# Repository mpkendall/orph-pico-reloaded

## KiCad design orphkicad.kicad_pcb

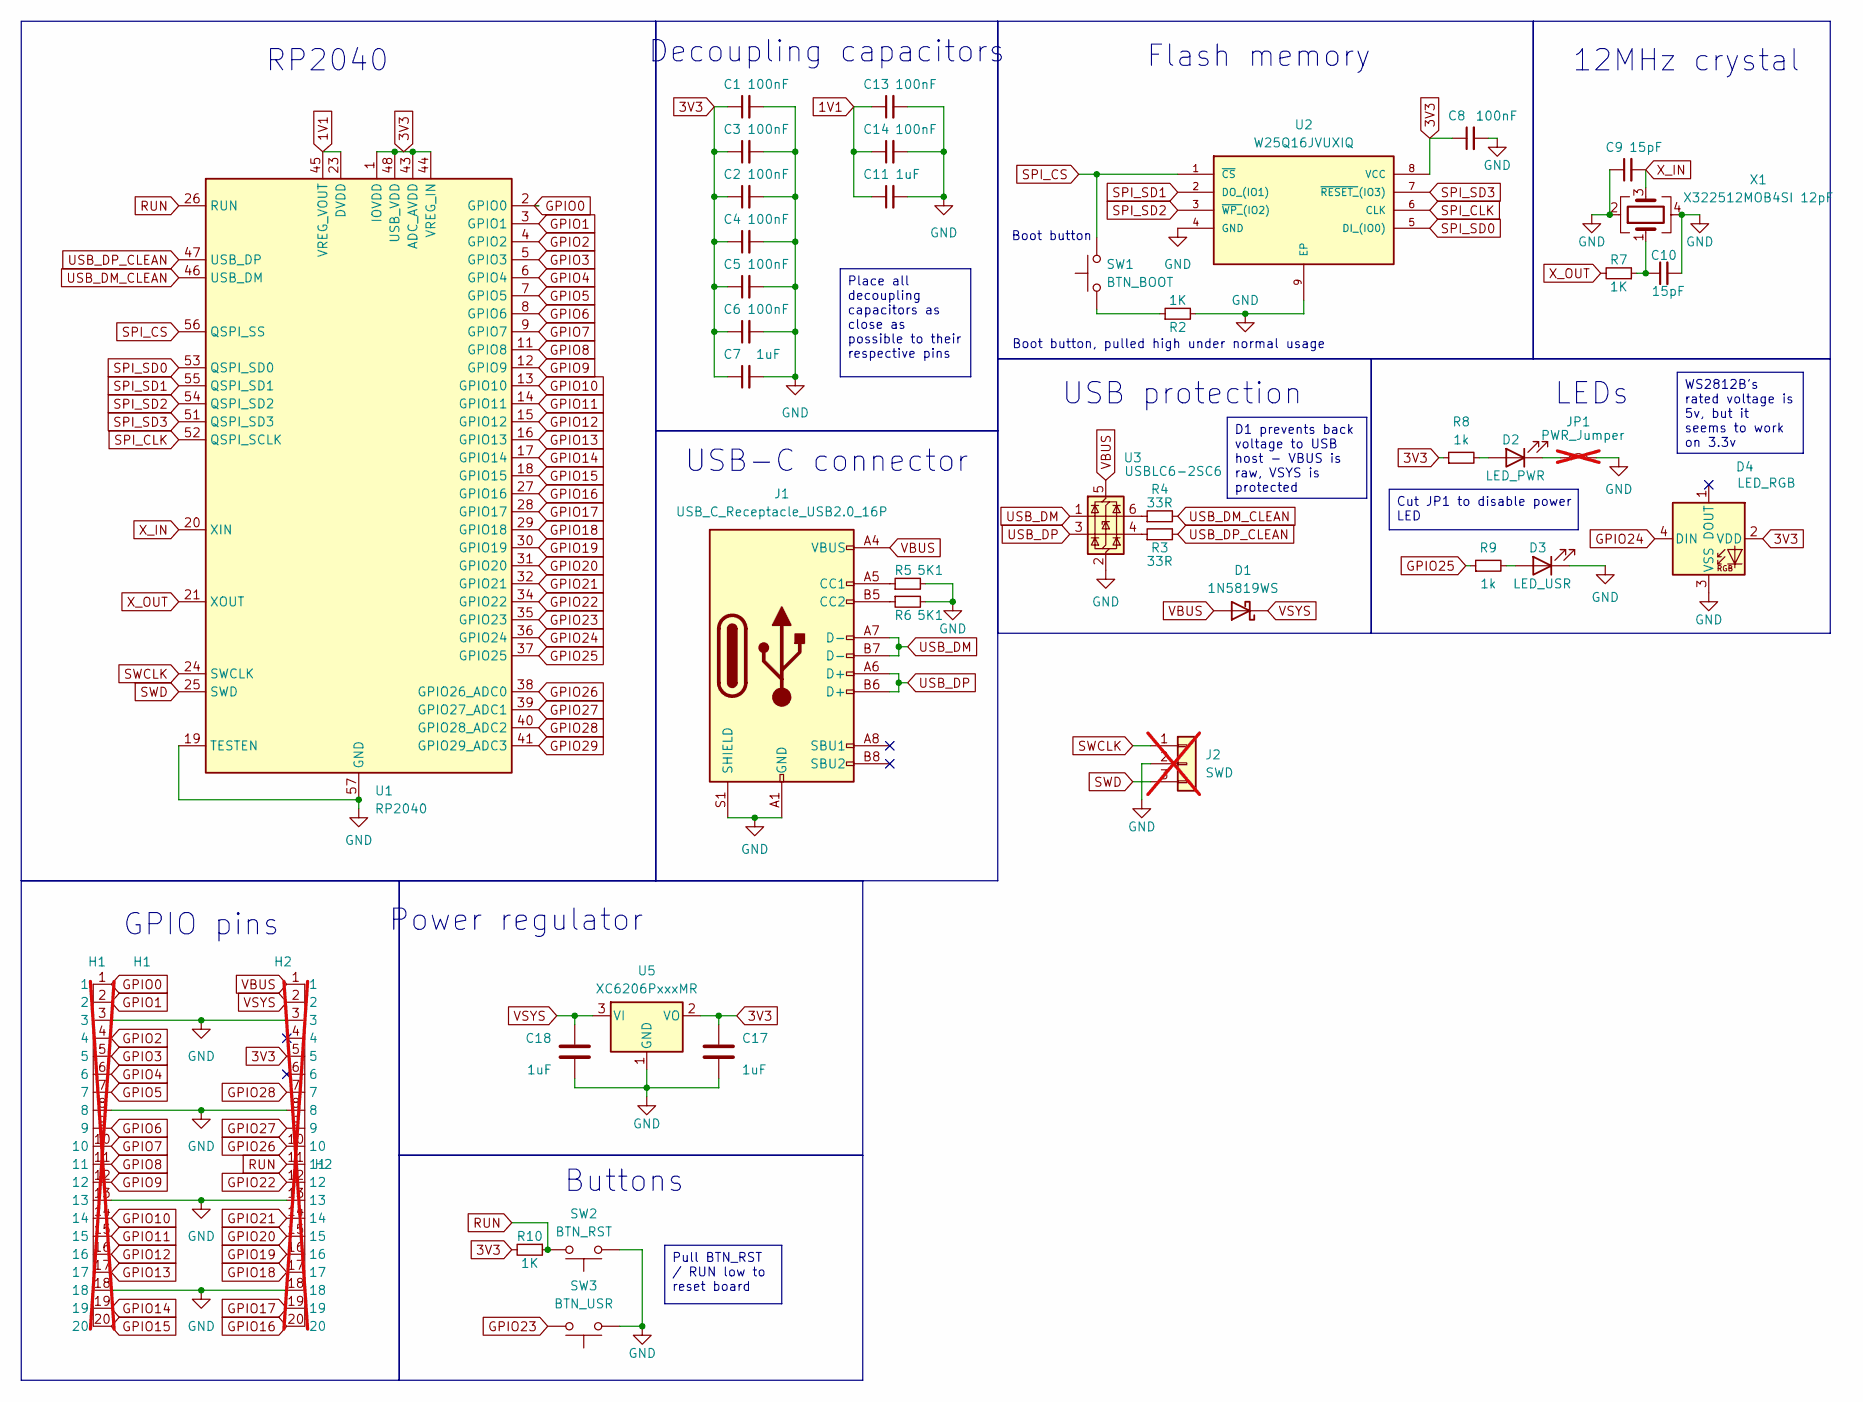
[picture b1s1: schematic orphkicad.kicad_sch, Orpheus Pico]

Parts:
C1, C2, C3, C4, C5, C6, C8, C13, C14: 100nF; C_0402_1005Metric; LCSC C1525
C7, C11, C17, C18: 1uF; C_0402_1005Metric; LCSC C52923
C9, C10: 15pF; C_0402_1005Metric; LCSC C1548
D1: 1N5819WS; D_SOD-323; LCSC C191023
D2: LED_PWR; LED_0603_1608Metric; LCSC C2286
D3: LED_USR; LED_0603_1608Metric; LCSC C2286
D4: LED_RGB; LED-SMD_4P-L1.6-W1.5_XL-1615RGBC-WS2812B; LCSC C5349954
H1: H1; OrphPicoHeaders; not fitted
H2: H2; OrphPicoHeaders; not fitted
J1: USB_C_Receptacle_USB2.0_16P; USB-C-SMD_TYPE-C-6PIN-2MD-073; LCSC C2765186
J2: SWD; PinHeader_1x03_P2.54mm_Vertical; not fitted
JP1: PWR_Jumper; SolderJumper-2_P1.3mm_Bridged2Bar_RoundedPad1.0x1.5mm; not fitted
R2, R7, R10: 1K; R_0402_1005Metric; LCSC C11702
R3, R4: 33R; R_0402_1005Metric; LCSC C25105
R5, R6: 5K1; R_0402_1005Metric; LCSC C25905
R8, R9: 1k; R_0402_1005Metric; LCSC C11702
SW1: BTN_BOOT; SW-SMD_L3.9-W3.0-P4.45; LCSC C455280
SW2: BTN_RST; SW-SMD_L3.9-W3.0-P4.45; LCSC C455280
SW3: BTN_USR; SW-SMD_L3.9-W3.0-P4.45; LCSC C455280
U1: RP2040; QFN-56-1EP_7x7mm_P0.4mm_EP3.2x3.2mm; LCSC C2040
U2: W25Q16JVUXIQ; Winbond_USON-8-1EP_3x2mm_P0.5mm_EP0.2x1.6mm; MANUFACTURER_PART_NUMBER W25Q16JVUXIQ; LCSC C2843335
U3: USBLC6-2SC6; SOT-23-6; LCSC C5180249
U5: XC6206PxxxMR; SOT-23-3; LCSC C5446
X1: X322512MOB4SI 12pF; Crystal_SMD_3225-4Pin_3.2x2.5mm; LCSC C70565

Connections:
1V1: C11.1, C13.1, C14.1, U1.23 (DVDD), U1.45 (VREG_VOUT), U1.50 (DVDD)
3V3: C1.1, C2.1, C3.1, C4.1, C5.1, C6.1, C7.1, C8.1, C17.1, D4.2 (VDD), H2.5, R8.1, R10.2, U1.1 (IOVDD), U1.10 (IOVDD), U1.22 (IOVDD), U1.33 (IOVDD), U1.42 (IOVDD), U1.43 (ADC_AVDD), U1.44 (VREG_IN), U1.48 (USB_VDD), U1.49 (IOVDD), U2.8 (VCC), U5.2 (VO)
GND: C1.2, C2.2, C3.2, C4.2, C5.2, C6.2, C7.2, C8.2, C9.1, C10.2, C11.2, C13.2, C14.2, C17.2, C18.2, D3.1 (K), D4.3 (VSS), H1.3, H1.8, H1.13, H1.18, H2.3, H2.8, H2.13, H2.18, J1.A1 (GND), J1.B1 (GND), J1.S1 (SHIELD), J2.2, JP1.2 (B), R2.2, R5.2, R6.2, SW2.1, SW3.1, U1.19 (TESTEN), U1.57 (GND), U2.4 (GND), U2.9 (EP), U3.2 (GND), U5.1 (GND), X1.2, X1.4
GPIO0: H1.1, U1.2 (GPIO0)
GPIO1: H1.2, U1.3 (GPIO1)
GPIO2: H1.4, U1.4 (GPIO2)
GPIO3: H1.5, U1.5 (GPIO3)
GPIO4: H1.6, U1.6 (GPIO4)
GPIO5: H1.7, U1.7 (GPIO5)
GPIO6: H1.9, U1.8 (GPIO6)
GPIO7: H1.10, U1.9 (GPIO7)
GPIO8: H1.11, U1.11 (GPIO8)
GPIO9: H1.12, U1.12 (GPIO9)
GPIO10: H1.14, U1.13 (GPIO10)
GPIO11: H1.15, U1.14 (GPIO11)
GPIO12: H1.16, U1.15 (GPIO12)
GPIO13: H1.17, U1.16 (GPIO13)
GPIO14: H1.19, U1.17 (GPIO14)
GPIO15: H1.20, U1.18 (GPIO15)
GPIO16: H2.20, U1.27 (GPIO16)
GPIO17: H2.19, U1.28 (GPIO17)
GPIO18: H2.17, U1.29 (GPIO18)
GPIO19: H2.16, U1.30 (GPIO19)
GPIO20: H2.15, U1.31 (GPIO20)
GPIO21: H2.14, U1.32 (GPIO21)
GPIO22: H2.12, U1.34 (GPIO22)
GPIO23: SW3.2, U1.35 (GPIO23)
GPIO24: D4.4 (DIN), U1.36 (GPIO24)
GPIO25: R9.1, U1.37 (GPIO25)
GPIO26: H2.10, U1.38 (GPIO26_ADC0)
GPIO27: H2.9, U1.39 (GPIO27_ADC1)
GPIO28: H2.7, U1.40 (GPIO28_ADC2)
GPIO29: U1.41 (GPIO29_ADC3)
unnamed: C10.1, R7.1, X1.1
unnamed: D2.2 (A), R8.2
unnamed: D2.1 (K), JP1.1 (A)
unnamed: D3.2 (A), R9.2
unnamed: J1.A5 (CC1), R5.1
unnamed: J1.B5 (CC2), R6.1
unnamed: R2.1, SW1.1
unnamed: R3.1, U3.4 (I/O2)
unnamed: R4.1, U3.6 (I/O1)
RUN: H2.11, R10.1, SW2.2, U1.26 (RUN)
SPI_CLK: U1.52 (QSPI_SCLK), U2.6 (CLK)
SPI_CS: SW1.2, U1.56 (QSPI_SS), U2.1 (~CS)
SPI_SD0: U1.53 (QSPI_SD0), U2.5 (DI_(IO0))
SPI_SD1: U1.55 (QSPI_SD1), U2.2 (DO_(IO1))
SPI_SD2: U1.54 (QSPI_SD2), U2.3 (~WP_(IO2))
SPI_SD3: U1.51 (QSPI_SD3), U2.7 (~RESET_(IO3))
SWCLK: J2.1, U1.24 (SWCLK)
SWD: J2.3, U1.25 (SWD)
USB_DM: J1.A7 (D-), J1.B7 (D-), U3.1 (I/O1)
USB_DM_CLEAN: R4.2, U1.46 (USB_DM)
USB_DP: J1.A6 (D+), J1.B6 (D+), U3.3 (I/O2)
USB_DP_CLEAN: R3.2, U1.47 (USB_DP)
VBUS: D1.2 (A), H2.1, J1.A4 (VBUS), J1.B4 (VBUS), U3.5 (VBUS)
VSYS: C18.1, D1.1 (K), H2.2, U5.3 (VI)
X_IN: C9.2, U1.20 (XIN), X1.3
X_OUT: R7.2, U1.21 (XOUT)

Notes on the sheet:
Power regulator
Flash memory
Boot button, pulled high under normal usage
USB-C connector
Decoupling capacitors
USB protection
LEDs
Boot button
RP2040
GPIO pins
Buttons
12MHz crystal
Pull BTN_RST / RUN low to reset board
Place all decoupling capacitors as close as possible to their respective pins
WS2812B's rated voltage is 5v, but it seems to work on 3.3v
Cut JP1 to disable power LED
D1 prevents back voltage to USB host - VBUS is raw, VSYS is protected

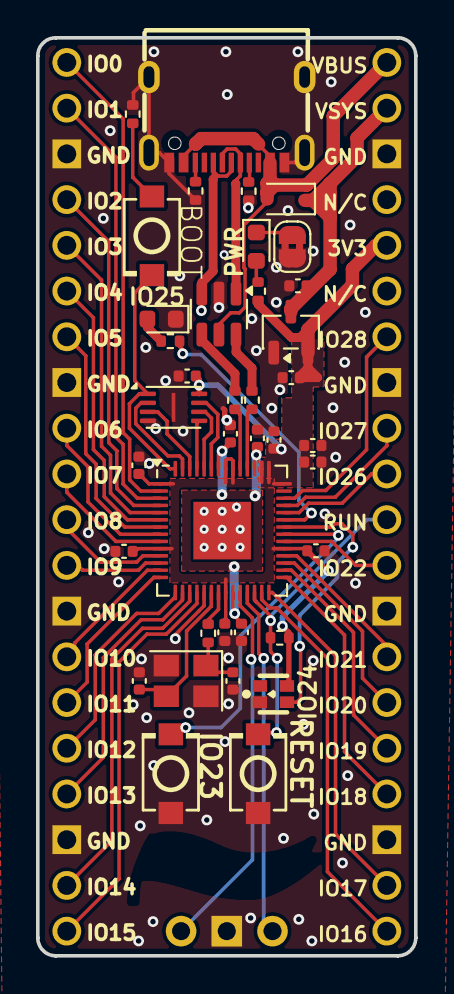
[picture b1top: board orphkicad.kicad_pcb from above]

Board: 2 copper layers, 21.0 x 51.0 mm, 41 parts (0 on the bottom side), 58 nets.

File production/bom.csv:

Designator,Footprint,Quantity,Value,LCSC Part #
"C1, C13, C14, C2, C3, C4, C5, C6, C8",0402,9,100nF,C1525
"C10, C9",0402,2,15pF,C1548
"C11, C17, C18, C7",0402,4,1uF,C52923
D1,D_SOD-323,1,1N5819WS,C191023
D2,0603,1,LED_PWR,C2286
D3,0603,1,LED_USR,C2286
D4,LED-SMD_4P-L1.6-W1.5_XL-1615RGBC-WS2812B,1,LED_RGB,C5349954
J1,USB-C-SMD_TYPE-C-6PIN-2MD-073,1,USB_C_Receptacle_USB2.0_16P,C2765186
"R10, R2, R7, R8, R9",0402,5,1K,C11702
"R3, R4",0402,2,33R,C25105
"R5, R6",0402,2,5K1,C25905
SW1,SW-SMD_L3.9-W3.0-P4.45,1,BTN_BOOT,C455280
SW2,SW-SMD_L3.9-W3.0-P4.45,1,BTN_RST,C455280
SW3,SW-SMD_L3.9-W3.0-P4.45,1,BTN_USR,C455280
U1,QFN-56-1EP_7x7mm_P0.4mm_EP3.2x3.2mm,1,RP2040,C2040
U2,Winbond_USON-8-1EP_3x2mm_P0.5mm_EP0.2x1.6mm,1,W25Q16JVUXIQ,C2843335
U3,SOT-23-6,1,USBLC6-2SC6,C5180249
U5,SOT-23-3,1,XC6206PxxxMR,C5446
X1,Crystal_SMD_3225-4Pin_3.2x2.5mm,1,X322512MOB4SI 12pF,C70565

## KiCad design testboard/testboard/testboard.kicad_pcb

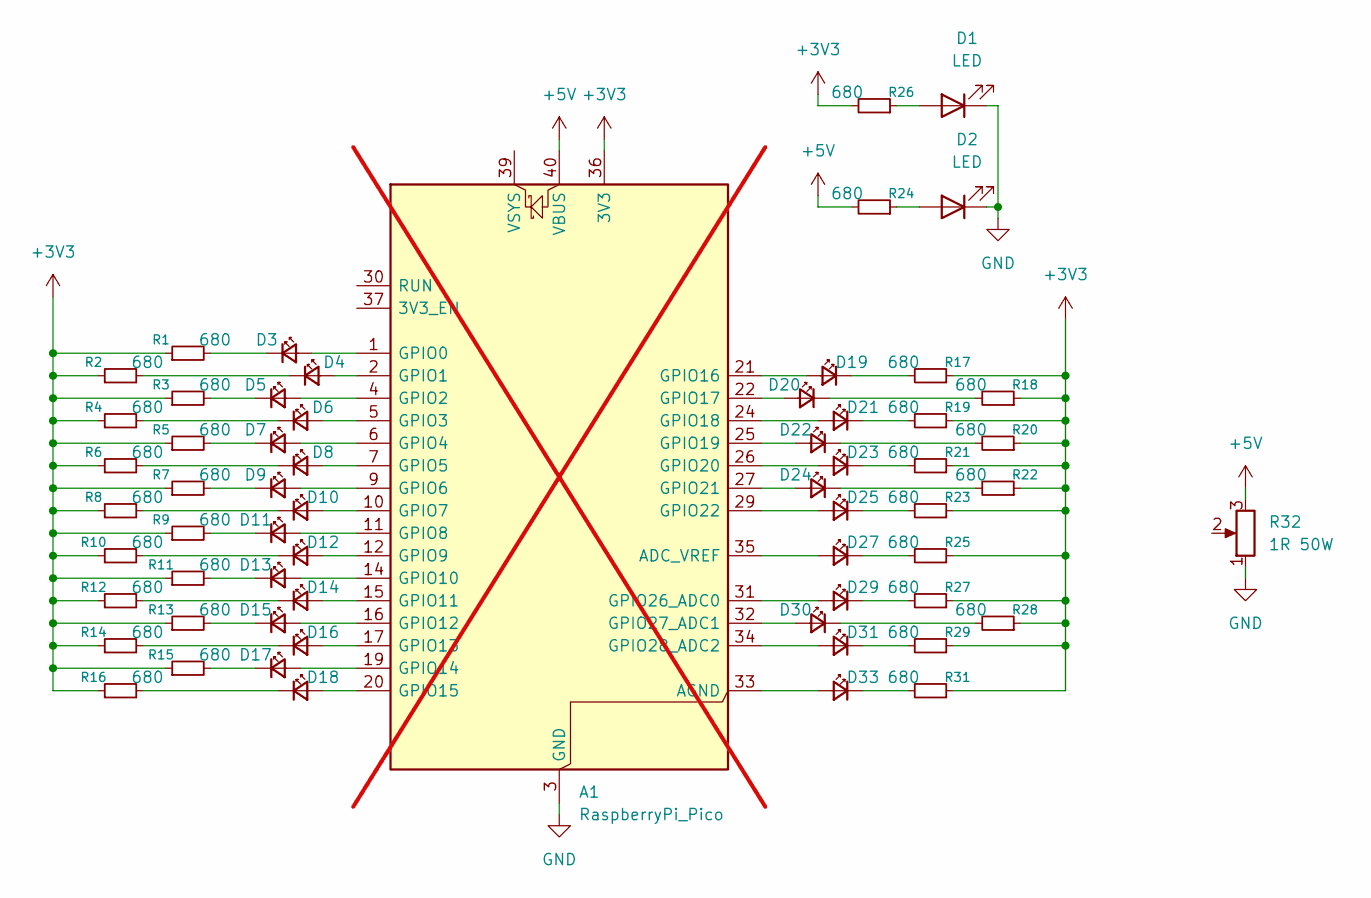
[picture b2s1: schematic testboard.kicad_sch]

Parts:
A1: RaspberryPi_Pico; RaspberryPi_Pico_Common_THT; not fitted
D1, D2, D3, D4, D5, D6, D7, D8, D9, D10, D11, D12, D13, D14, D15, D16, D17, D18, D19, D20, D21, D22, D23, D24, D25, D27, D29, D30, D31, D33: LED; LED_0603_1608Metric; LCSC Part # C2290
R1, R2, R3, R4, R5, R6, R7, R8, R9, R10, R11, R12, R13, R14, R15, R16, R17, R18, R19, R20, R21, R22, R23, R24, R25, R26, R27, R28, R29, R31: 680; R_0603_1608Metric; LCSC Part # C23228
R32: 1R 50W; TO-263-2; LCSC Part # C39221240

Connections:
+3V3: A1.36 (3V3), R1.1, R2.1, R3.1, R4.1, R5.1, R6.1, R7.1, R8.1, R9.1, R10.1, R11.1, R12.1, R13.1, R14.1, R15.1, R16.1, R17.1, R18.1, R19.1, R20.1, R21.1, R22.1, R23.1, R25.1, R26.2, R27.1, R28.1, R29.1, R31.1
+5V: A1.40 (VBUS), R24.2, R32.3
GND: A1.3 (GND), A1.8 (GND), A1.13 (GND), A1.18 (GND), A1.23 (GND), A1.28 (GND), A1.38 (GND), D1.1 (K), D2.1 (K), R32.1
unnamed: A1.35 (ADC_VREF), D27.2 (A)
unnamed: A1.33 (AGND), D33.2 (A)
unnamed: A1.1 (GPIO0), D3.2 (A)
unnamed: A1.2 (GPIO1), D4.2 (A)
unnamed: A1.4 (GPIO2), D5.2 (A)
unnamed: A1.5 (GPIO3), D6.2 (A)
unnamed: A1.6 (GPIO4), D7.2 (A)
unnamed: A1.7 (GPIO5), D8.2 (A)
unnamed: A1.9 (GPIO6), D9.2 (A)
unnamed: A1.10 (GPIO7), D10.2 (A)
unnamed: A1.11 (GPIO8), D11.2 (A)
unnamed: A1.12 (GPIO9), D12.2 (A)
unnamed: A1.14 (GPIO10), D13.2 (A)
unnamed: A1.15 (GPIO11), D14.2 (A)
unnamed: A1.16 (GPIO12), D15.2 (A)
unnamed: A1.17 (GPIO13), D16.2 (A)
unnamed: A1.19 (GPIO14), D17.2 (A)
unnamed: A1.20 (GPIO15), D18.2 (A)
unnamed: A1.21 (GPIO16), D19.2 (A)
unnamed: A1.22 (GPIO17), D20.2 (A)
unnamed: A1.24 (GPIO18), D21.2 (A)
unnamed: A1.25 (GPIO19), D22.2 (A)
unnamed: A1.26 (GPIO20), D23.2 (A)
unnamed: A1.27 (GPIO21), D24.2 (A)
unnamed: A1.29 (GPIO22), D25.2 (A)
unnamed: A1.31 (GPIO26_ADC0), D29.2 (A)
unnamed: A1.32 (GPIO27_ADC1), D30.2 (A)
unnamed: A1.34 (GPIO28_ADC2), D31.2 (A)
unnamed: D1.2 (A), R26.1
unnamed: D2.2 (A), R24.1
unnamed: D3.1 (K), R1.2
unnamed: D4.1 (K), R2.2
unnamed: D5.1 (K), R3.2
unnamed: D6.1 (K), R4.2
unnamed: D7.1 (K), R5.2
unnamed: D8.1 (K), R6.2
unnamed: D9.1 (K), R7.2
unnamed: D10.1 (K), R8.2
unnamed: D11.1 (K), R9.2
unnamed: D12.1 (K), R10.2
unnamed: D13.1 (K), R11.2
unnamed: D14.1 (K), R12.2
unnamed: D15.1 (K), R13.2
unnamed: D16.1 (K), R14.2
unnamed: D17.1 (K), R15.2
unnamed: D18.1 (K), R16.2
unnamed: D19.1 (K), R17.2
unnamed: D20.1 (K), R18.2
unnamed: D21.1 (K), R19.2
unnamed: D22.1 (K), R20.2
unnamed: D23.1 (K), R21.2
unnamed: D24.1 (K), R22.2
unnamed: D25.1 (K), R23.2
unnamed: D27.1 (K), R25.2
unnamed: D29.1 (K), R27.2
unnamed: D30.1 (K), R28.2
unnamed: D31.1 (K), R29.2
unnamed: D33.1 (K), R31.2

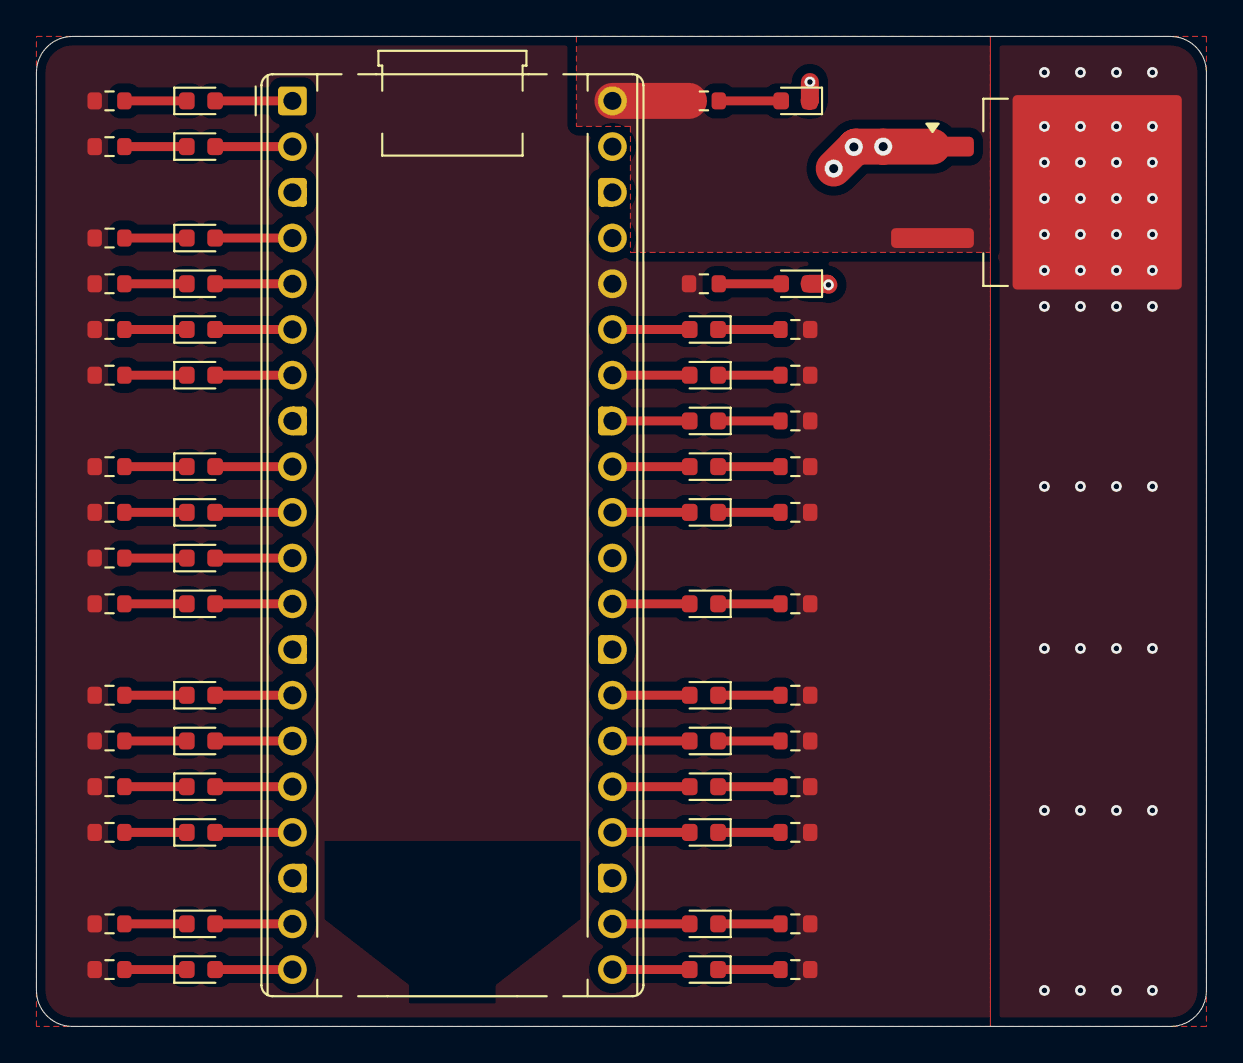
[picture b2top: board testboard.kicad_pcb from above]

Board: 2 copper layers, 65.0 x 55.0 mm, 62 parts (0 on the bottom side), 61 nets.

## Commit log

2026-01-10 Add .gitignore
2026-01-10 clean up some routing
2026-01-11 improve routing on esd protection ic
2026-01-18 minor fixes + stitching vias
2026-01-19 make field show up nice
2026-01-19 updated dnp
2026-01-20 Test board and fix silk
2026-01-20 FIXIEMIDNWJKE
2026-01-21 fix silkscreen label
2026-01-24 actual production files
2026-01-25 Move BOOT label
2026-01-25 Remove extra space from LCSC Part #
